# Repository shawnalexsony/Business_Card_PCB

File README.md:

# Business Card PCB
A personal <b>Business Card</b> designed as a <b>PCB</b>. It contains an integrated <b>NFC</b> tag to share contact information wirelessly, and uses energy harvesting from NFC field to light up the LED circuitry!! 

The heart of this PCB is the <b>NFC</b> controller IC, the <b>NT3H1101</b> from <b>NXP Semiconductors</b>.

<b>NFC (Near Field Communication)</b> is a short-range radio technology that enables communication between devices that are held in close proximity (< 10 cm). NFC systems are based on traditional High Frequency (HF) RFID, operating at 13.56 MHz

You can store your contact information, link to your portfolio, social media, and so on, the choice is Yours!!

The form factor is maintained as a standard credit/debit card, so you can carry it around normally in your wallet.

The Schematics and PCB design is done with <b>KiCAD</b>, the Vector graphics is done with <b>Inkscape</b>.

I used the "Bitmap to Component Convertor" tool built in <b>KiCAD</b> to import my custom font text, Logo, QR code, etc. I imported them as Soldermask and Copper layer so that they'll be visible with nice HASL/ENIG finish. 
My suggestion would be to minimize the use of silkscreen, as the silkscreen print might not be of good quality for complex graphics.

The NFC tag programming was done with Tagwriter app from <b>NXP</b>. This app has multiple options to write Website Links, Phone number, Email, etc into the NTAG IC which you can customize as per your requirement.

While doing the PCB layout, please make sure you import the <b>NFC antenna</b> correctly. NXP semiconductors have a detailed guide on different types of NFC antennas and their layout template. The rest of the circuit can be done as per your design. 
<br><br>
<i>Note : Please make sure there is no Copper under the Antenna region, Best option is to define a custom keepout area so that you won't mess up the Antenna performance.</i>
<br>

Feel free to use this as a reference and design your own Business Card PCBs!! Good Luck!! :)

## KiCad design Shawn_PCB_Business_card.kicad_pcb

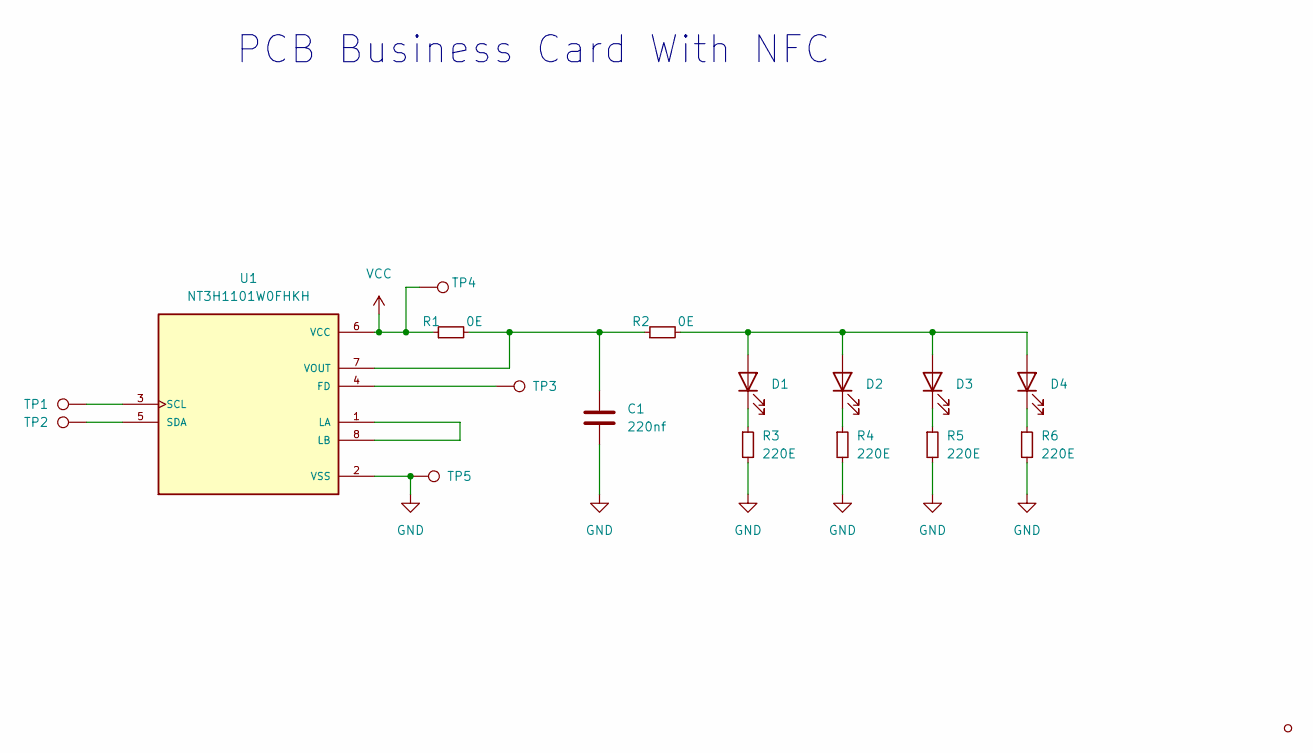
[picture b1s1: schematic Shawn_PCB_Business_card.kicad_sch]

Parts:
C1: 220nf; C_0402_1005Metric
D1, D2, D3, D4: LED; LED_0402_1005Metric
R1, R2: 0E; R_0402_1005Metric
R3, R4, R5, R6: 220E; R_0402_1005Metric
TP1, TP2, TP3, TP4, TP5: TestPoint; TestPoint_Pad_D1.0mm
TP6: TestPoint_Small
U1: NT3H1101W0FHKH; IC_NT3H1101W0FHKH; PARTREV 3.3

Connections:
GND: C1.2, R3.2, R4.2, R5.2, R6.2, TP5.1, U1.2 (VSS)
unnamed: C1.1, R1.2, R2.1, U1.7 (VOUT)
unnamed: D1.1 (K), R3.1
unnamed: D1.2 (A), D2.2 (A), D3.2 (A), D4.2 (A), R2.2
unnamed: D2.1 (K), R4.1
unnamed: D3.1 (K), R5.1
unnamed: D4.1 (K), R6.1
unnamed: TP1.1, U1.3 (SCL)
unnamed: TP2.1, U1.5 (SDA)
unnamed: TP3.1, U1.4 (FD)
unnamed: U1.1 (LA), U1.8 (LB)
VCC: R1.1, TP4.1, U1.6 (VCC)

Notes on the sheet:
PCB Business Card With NFC

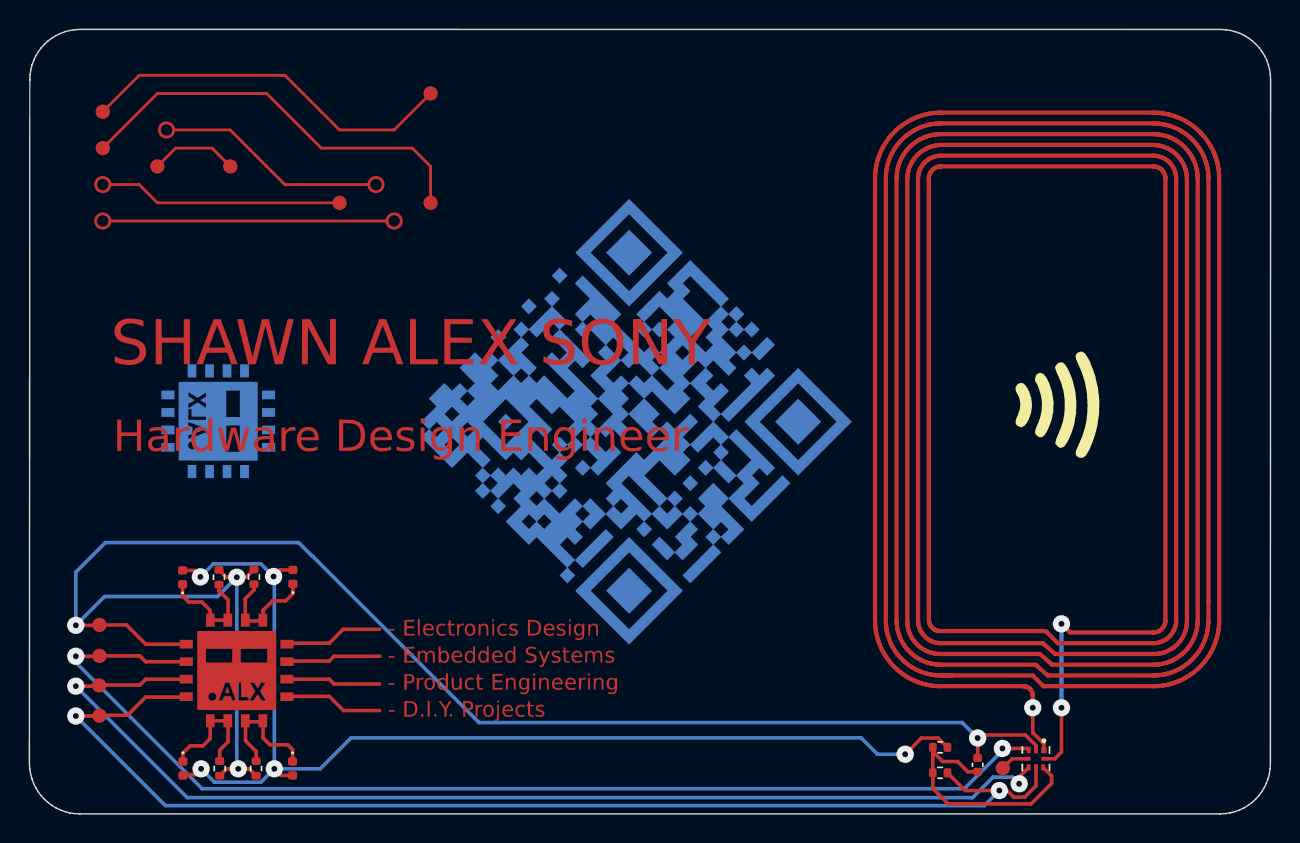
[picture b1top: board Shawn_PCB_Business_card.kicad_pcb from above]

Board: 2 copper layers, 86.6 x 54.7 mm, 17 parts (0 on the bottom side), 12 nets.

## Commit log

2023-01-16 Added source files
2023-01-25 added License
